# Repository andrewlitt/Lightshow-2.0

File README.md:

# Lightshow-2.0
KiCAD Project Files for a PCB to control LED's through Music! Uses MSGEQ7 + ATmega328P w/ an Arduino Bootloader!

[I wrote about this project on my blog!](https://alitt.ca/blog/led-music/)

![alt text][render]

[render]: https://andrewlitt.github.io/2019/08/11/LED-Music/header.png "PCB Rendering"

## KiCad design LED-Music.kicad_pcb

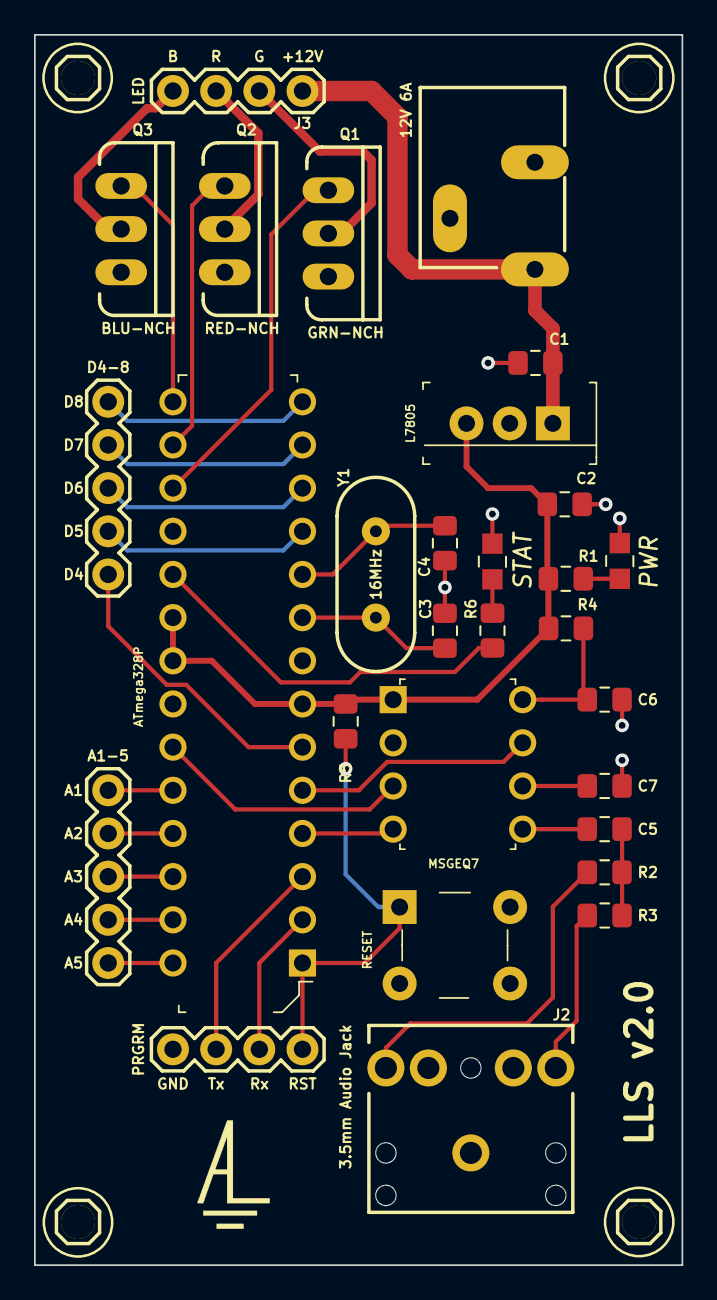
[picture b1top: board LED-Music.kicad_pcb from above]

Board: 2 copper layers, 38.1 x 72.4 mm, 34 parts (0 on the bottom side), 36 nets.

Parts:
 : 1X01
 #2,  #3,  #4: 1X01
ATmega328P: ATMEGA328P; DIP-28_W7.62mm
C1, C2: 10uF; C_0805_2012Metric_Pad1.15x1.40mm_HandSolder
C3, C4: 22p; C_0805_2012Metric_Pad1.15x1.40mm_HandSolder
C5, C7: 0.1u; C_0805_2012Metric_Pad1.15x1.40mm_HandSolder
C6: 33p; C_0805_2012Metric_Pad1.15x1.40mm_HandSolder
J1: 12V 6A; POWER_JACK_SLOT
J2: 3.5mm Audio Jack; AUDIO-JACK
J3: LED; 1X04
J4: A1-5; 1X05
J5: PRGRM; 1X04
J6: D4-8; 1X05
L7805: L7805CV; TO-220-3
MSGEQ7: MSGEQ7; DIP-8_W7.62mm
PWR: LED; 0805
Q1: GRN-NCH; TO220V
Q2: RED-NCH; TO220V
Q3: BLU-NCH; TO220V
R1, R6: 220; R_0805_2012Metric_Pad1.15x1.40mm_HandSolder
R2, R3: 22k; R_0805_2012Metric_Pad1.15x1.40mm_HandSolder
R4: 200k; R_0805_2012Metric_Pad1.15x1.40mm_HandSolder
R5: 10k; R_0805_2012Metric_Pad1.15x1.40mm_HandSolder
RESET: SW400-ND; Switch_Tactile_THT_B3F-1xxx
STAT: LED; 0805
Y1: 16MHz; HC49US
m: LOGO; logo

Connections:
+5V: ATmega328P.7, ATmega328P.20, ATmega328P.21, C2.1, L7805.3, MSGEQ7.1, R1.2, R4.1, R5.2
+12V: C1.1, J1.PWR, J3.1, L7805.1
/Rx: ATmega328P.2, J5.2
/Tx: ATmega328P.3, J5.3
AUDIO_IN: C5.1, MSGEQ7.5
GND: ATmega328P.8, ATmega328P.22, C1.2, C2.2, C3.2, C4.2, C6.1, C7.2, J1.GND@, J2.RSH, J2.SLEE, J2.TSH, J5.4, L7805.2, MSGEQ7.2, PWR.2, Q1.3, Q2.3, Q3.3, RESET.3, RESET.4, STAT.2
MSGEQ7_OUT: ATmega328P.23, MSGEQ7.3
unnamed: ATmega328P.9, C3.1, Y1.1
unnamed: ATmega328P.10, C4.1, Y1.2
unnamed: C5.2, R2.1, R3.1
unnamed: C6.2, MSGEQ7.8, R4.2
unnamed: C7.1, MSGEQ7.6
unnamed: J2.RING, R2.2
unnamed: J2.TIP, R3.2
unnamed: J3.2, Q1.2
unnamed: J3.3, Q2.2
unnamed: J3.4, Q3.2
unnamed: ATmega328P.24, J4.1
unnamed: ATmega328P.25, J4.2
unnamed: ATmega328P.26, J4.3
unnamed: ATmega328P.27, J4.4
unnamed: ATmega328P.28, J4.5
unnamed: ATmega328P.6, J6.1
unnamed: ATmega328P.11, J6.2
unnamed: ATmega328P.12, J6.3
unnamed: ATmega328P.13, J6.4
unnamed: ATmega328P.14, J6.5
unnamed: PWR.1, R1.1
unnamed: R6.1, STAT.1
unnamed: ATmega328P.19, R6.2
RESET: ATmega328P.5, MSGEQ7.7
RST: ATmega328P.1, J5.1, R5.1, RESET.1
STROBE: ATmega328P.4, MSGEQ7.4
Vg_Q1: ATmega328P.17, Q1.1
Vg_Q2: ATmega328P.16, Q2.1
Vg_Q3: ATmega328P.15, Q3.1

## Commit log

2019-07-31 Project Upload
2025-02-19 IMP: Update to KiCAD 8.0 File Formats
